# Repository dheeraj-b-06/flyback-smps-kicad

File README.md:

# 12V 5A (60 W) Isolated Flyback SMPS

An offline, isolated switch-mode power supply designed in **KiCad 9.0**. It converts AC mains into a regulated **12 V DC output at up to 5 A** using a flyback converter with secondary-side regulation (TL431 + optocoupler).

> ⚠️ **Mains voltage warning:** this circuit connects directly to AC mains and has lethal voltages (up to ~400 V DC) on the primary side. Only build or test it if you are experienced with mains-connected electronics.

## Specifications

| Parameter | Value |
|---|---|
| Output | 12 V DC, 5 A (60 W) |
| Topology | Isolated flyback |
| PWM controller | OB2273 (current-mode, SOT-23-6) |
| Power switch | SVF12N65F (650 V N-MOSFET) |
| Transformer | EFD30 core, custom wound |
| Output rectifier | MBRF30100 dual Schottky |
| Feedback | TL431 + EL817C optocoupler |
| Primary-secondary clearance | 6 mm (enforced by custom DRC rules) |
| PCB | 2-layer, 1.6 mm |

## Block diagram

```mermaid
flowchart LR
    AC[AC mains] --> IN[Fuse, NTC, varistor,<br/>X-cap, CM choke]
    IN --> BR[Bridge rectifier<br/>+ 400 V bulk cap]
    BR --> T[Flyback transformer T2]
    T --> Q[MOSFET Q1]
    Q --> RS[Sense resistor R8]
    T --> D[Schottky D4]
    D --> F[LC filter<br/>+ output caps]
    F --> OUT[12 V / 5 A]
    F --> TL[TL431 voltage divider]
    TL --> OPT[Optocoupler EL817C]
    OPT -->|FB| IC[OB2273 PWM controller]
    RS -->|current sense| IC
    IC -->|gate drive| Q
    T -.->|aux winding| IC
```

## How it works

### 1. Input stage and rectification
Mains enters through terminal block **J1** and a **1 A fuse (F1)**. The **varistor (R1)** clamps surges, the **X-capacitor (C1, 100 nF / 275 VAC)** and the **common-mode choke (T1)** filter conducted noise, and the **NTC thermistor (R2)** limits the inrush current when the bulk capacitor charges. The **KBP410 bridge (BR1)** rectifies the AC and the **120 µF / 400 V capacitor (C2)** smooths it into a high-voltage DC rail (the `DCLINE` net, roughly 310–340 V DC at 230 V AC input).

### 2. Start-up and controller supply
When power is first applied, the OB2273 has no supply. **R3 and R4** (470 kΩ each, in series) trickle current from the DC rail into the VDD pin, charging **C5 (47 µF)** and **C6 (1 µF)**. Once VDD reaches the start-up threshold, the controller begins switching.

After start-up, the **auxiliary winding** on T2 (pins 4 and 6) takes over: diode **D2 (FR107)** and resistor **R9** rectify it to keep VDD alive without the wasteful start-up resistors. **D3 (24 V zener)** clamps VDD to protect the controller from overvoltage.

### 3. Switching and energy transfer (flyback action)
The OB2273 is a current-mode PWM controller. Its switching frequency is set by **R10** (100 kΩ) on the RI pin. It drives the gate of **Q1 (SVF12N65F)** through gate resistor **R6 (10 Ω)**.

- **MOSFET ON:** current ramps up through the primary winding of T2 and energy is stored in the transformer core. The secondary diode is reverse-biased, so the output capacitors alone supply the load.
- **MOSFET OFF:** the transformer voltage reverses, the Schottky **D4 (MBRF30100)** conducts, and the stored energy is delivered to the secondary, charging the output capacitors and feeding the load.

The transformer provides **galvanic isolation** between the mains-side primary and the safe-voltage secondary.

### 4. Current sensing and protection
Primary current flows through **R8 (0.2 Ω)** to ground. The resulting voltage is fed to the SENSE pin through **R7 (100 Ω)** and **C4 (100 pF)**, which form a low-pass filter that suppresses the turn-on spike. The controller ends each cycle when the peak current reaches its limit, giving **cycle-by-cycle overcurrent protection**.

### 5. Snubber / clamp
When Q1 turns off, the transformer's leakage inductance causes a voltage spike on the drain. The **RCD clamp** formed by **D1 (FR207), R5 (33 kΩ) and C3 (3.3 nF / 630 V)** absorbs this energy, keeping the drain voltage within the MOSFET's 650 V rating.

### 6. Output filtering
The Schottky output is smoothed by **C10 (2200 µF) and C11 (1000 µF)**, then passed through the **3.3 µH inductor (L1)** and **C12 (470 µF)** to reduce high-frequency ripple. **R16 (470 Ω)** acts as a small preload, and **R17 with LED D5** gives a power-on indicator.

### 7. Voltage regulation (feedback loop)
The output voltage is regulated on the secondary side:

1. A resistor divider (**R13** from the output, **R14** and trimmer **R15** to ground) feeds a fraction of the output voltage to the reference pin of the **TL431 (U1)**. The output voltage is set by

   `Vout ≈ Vref × (1 + R13 / R_bottom)`, where Vref ≈ 2.5 V

   and the **trimmer R15 fine-tunes** the final output.
2. If the output rises above target, the TL431 conducts harder and increases the current through the **optocoupler LED (OP1)**. Resistors **R11 and R12** set the bias, and **C8 (100 nF)** provides loop compensation.
3. The optocoupler's transistor pulls the controller's **FB pin** down, filtered by **C7 (10 nF)**, which tells the OB2273 to deliver less energy per cycle. If the output falls, the opposite happens.

Because the optocoupler transmits the error signal by light, the feedback loop crosses the isolation barrier without any electrical connection.

### 8. Isolation and EMI
The primary ground (`GND-1`) and secondary ground (`GND-2`) are separate. The only deliberate bridge between them is the **Y-capacitor C9 (2.2 nF / 250 VAC)**, which provides a return path for common-mode noise. Custom KiCad design rules enforce a **6 mm clearance** between primary-side and secondary-side copper.

## Key components

| Ref | Part | Function |
|---|---|---|
| F1 | 1 A fuse | Overcurrent protection |
| R1 | Varistor B72207S0271K101 | Surge protection |
| R2 | NTC 5D-11 | Inrush current limiting |
| C1 | 100 nF / 275 VAC | X-capacitor (differential EMI filter) |
| T1 | UU9.8 common-mode choke | Common-mode EMI filter |
| BR1 | KBP410 | Bridge rectifier |
| C2 | 120 µF / 400 V | Bulk capacitor |
| IC1 | OB2273 | Current-mode PWM controller |
| Q1 | SVF12N65F | 650 V power MOSFET |
| R8 | 0.2 Ω | Primary current sense |
| D1, R5, C3 | FR207, 33 kΩ, 3.3 nF | RCD snubber / clamp |
| T2 | EFD30 (6+6) | Flyback transformer (isolation) |
| D4 | MBRF30100 | Secondary Schottky rectifier |
| C10, C11, C12, L1 | 2200 µF, 1000 µF, 470 µF, 3.3 µH | Output filter |
| U1 | TL431 | Voltage reference / error amplifier |
| OP1 | EL817C | Optocoupler (isolated feedback) |
| R15 | 1 kΩ trimmer | Output voltage adjustment |
| C9 | 2.2 nF / 250 VAC | Y-capacitor |

## Repository contents

| File / folder | Description |
|---|---|
| `SMPS_12V_5A.kicad_sch` | Schematic |
| `SMPS_12V_5A.kicad_pcb` | PCB layout |
| `SMPS_12V_5A.kicad_pro` | KiCad project file |
| `SMPS_12V_5A.kicad_dru` | Custom design rules (isolation clearance) |
| `libs/lcsc/` | Imported LCSC symbols, footprints and 3D models |
| `mysmps.pretty/` | Custom footprints (transformer, 400 V capacitor) |

Open `SMPS_12V_5A.kicad_pro` in KiCad 9.0 or newer to view the design.

## Status

- [x] Schematic
- [x] PCB layout
- [ ] Prototype built
- [ ] Full-load testing

## Author

**Dheeraj**

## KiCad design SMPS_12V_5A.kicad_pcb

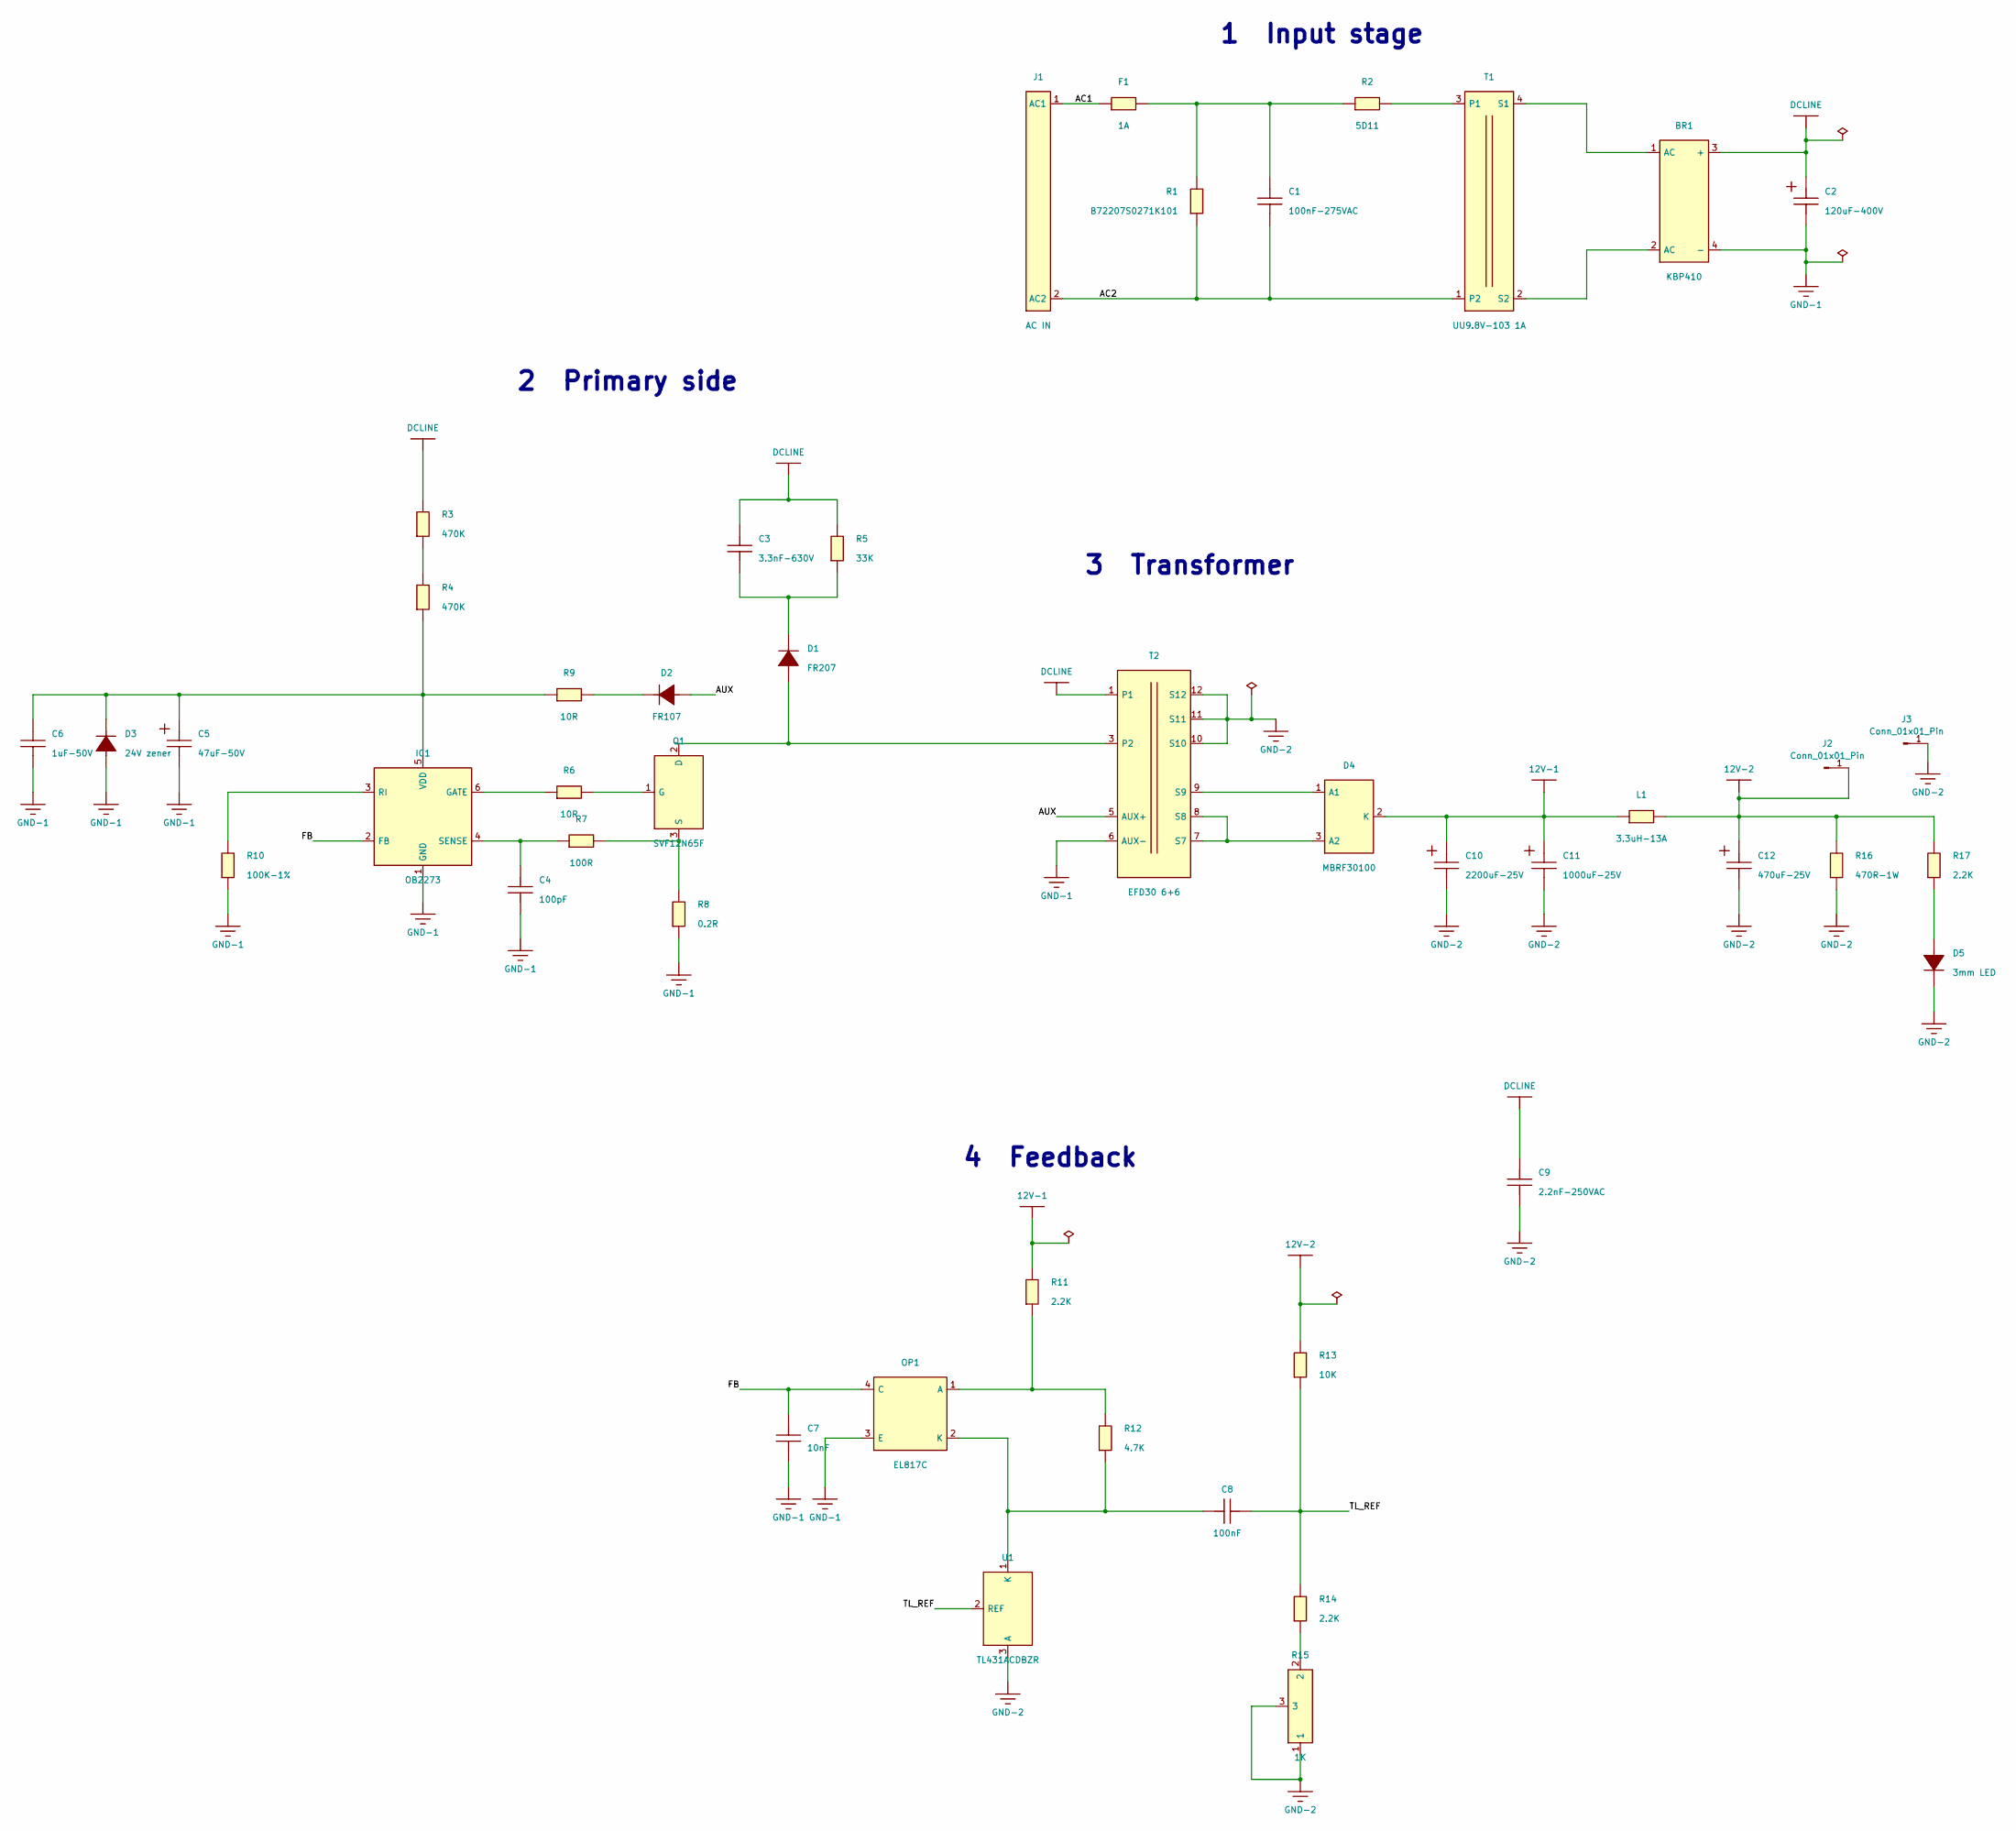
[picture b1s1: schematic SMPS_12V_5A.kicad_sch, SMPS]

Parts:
BR1: KBP410; C382768_KBP_4P-L14_5-W3_5-P3_81-L
C1: 100nF-275VAC; C_Rect_L18.0mm_W6.0mm_P15.00mm_FKS3_FKP3
C2: 120uF-400V; C_Box_P7.62mm_18x32.5mm
C3: 3.3nF-630V; C_1206_3216Metric
C4: 100pF; C_0805_2012Metric
C5: 47uF-50V; C_Radial_D6.3mm_H7.0mm_P2.50mm
C6: 1uF-50V; C_0805_2012Metric
C7: 10nF; C_0805_2012Metric
C8: 100nF; C_0805_2012Metric
C9: 2.2nF-250VAC; C_Disc_D7.0mm_W2.5mm_P5.00mm
C10: 2200uF-25V; C_Radial_D12.5mm_H20.0mm_P5.00mm
C11: 1000uF-25V; C_Radial_D10.0mm_H12.5mm_P5.00mm
C12: 470uF-25V; C_Radial_D8.0mm_H7.0mm_P3.50mm
D1: FR207; D_DO-15_P12.70mm_Horizontal
D2: FR107; D_DO-41_SOD81_P10.16mm_Horizontal
D3: 24V zener; D_MiniMELF
D4: MBRF30100; TO-220F-3_Vertical
D5: 3mm LED; LED_D3.0mm
F1: 1A; C3098_FUSE-TH_L8_5-W4_0-P5_08-D0_6
IC1: OB2273; SOT-23-6
J1: AC IN; TerminalBlock_bornier-2_P5.08mm
J2, J3: Conn_01x01_Pin; SolderWire-1.5sqmm_1x01_D1.7mm_OD3mm
L1: 3.3uH-13A; L_Wuerth_HCI-1350
OP1: EL817C; DIP-4_W7.62mm
Q1: SVF12N65F; TO-220F-3_Vertical
R1: B72207S0271K101; C125493_RES-TH_L9_0-W4_6-P5_00-D0_9-S3_4
R2: 5D11; RV_Disc_D9mm_W3.8mm_P5mm
R3, R4: 470K; R_1206_3216Metric
R5: 33K; R_2512_6332Metric
R6: 10R; R_0805_2012Metric
R7: 100R; R_0805_2012Metric
R8: 0.2R; R_2512_6332Metric
R9: 10R; R_1206_3216Metric
R10: 100K-1%; R_0805_2012Metric
R11, R14, R17: 2.2K; R_0805_2012Metric
R12: 4.7K; R_0805_2012Metric
R13: 10K; R_0805_2012Metric
R15: 1K; Potentiometer_Bourns_3296W_Vertical
R16: 470R-1W; R_2512_6332Metric
T1: UU9.8V-103 1A; C5276603_FILTER-TH_CMI-UU9_8-25MH
T2: EFD30 6+6; Transformer_EE_12pin_P5.08mm_Row27.56mm
U1: TL431ACDBZR; SOT-23

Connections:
12V-1: C10.1, C11.1, D4.2 (K), L1.1, R11.1
12V-2: C12.1, J2.1, L1.2, R13.1, R16.1, R17.1
/AC1: F1.1, J1.1 (AC1)
/AC2: C1.2, J1.2 (AC2), R1.2, T1.1 (P2)
/AUX: D2.2, T2.5 (AUX+)
/FB: C7.1, IC1.2 (FB), OP1.4 (C)
/TL_REF: C8.2, R13.2, R14.1, U1.2 (REF)
DCLINE: BR1.3 (+), C2.1, C3.1, C9.1, R3.1, R5.1, T2.1
GND-1: BR1.4 (-), C2.2, C4.2, C5.2, C6.2, C7.2, D3.2, IC1.1 (GND), OP1.3 (E), R8.2, R10.2, T2.6 (AUX-)
GND-2: C9.2, C10.2, C11.2, C12.2, D5.1, J3.1, R15.1, R15.3, R16.2, T2.10 (S10), T2.11 (S11), T2.12 (S12), U1.3 (A)
unnamed: C1.1, F1.2, R1.1, R2.1
unnamed: C3.2, D1.1, R5.2
unnamed: D2.1, R9.2
unnamed: D4.1 (A1), T2.9 (S9)
unnamed: D4.3 (A2), T2.7 (S7), T2.8 (S8)
unnamed: D5.2, R17.2
unnamed: IC1.6 (GATE), R6.1
unnamed: IC1.3 (RI), R10.1
unnamed: C4.1, IC1.4 (SENSE), R7.1
unnamed: C5.1, C6.1, D3.1, IC1.5 (VDD), R4.2, R9.1
unnamed: OP1.1 (A), R11.2, R12.1
unnamed: C8.1, OP1.2 (K), R12.2, U1.1 (K)
unnamed: D1.2, Q1.2 (D), T2.3 (P2)
unnamed: Q1.1 (G), R6.2
unnamed: Q1.3 (S), R7.2, R8.1
unnamed: R3.2, R4.1
unnamed: R14.2, R15.2
unnamed: R2.2, T1.3 (P1)
unnamed: BR1.1 (AC), T1.4 (S1)
unnamed: BR1.2 (AC), T1.2 (S2)

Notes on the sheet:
2 Primary side
1 Input stage
3 Transformer
4 Feedback

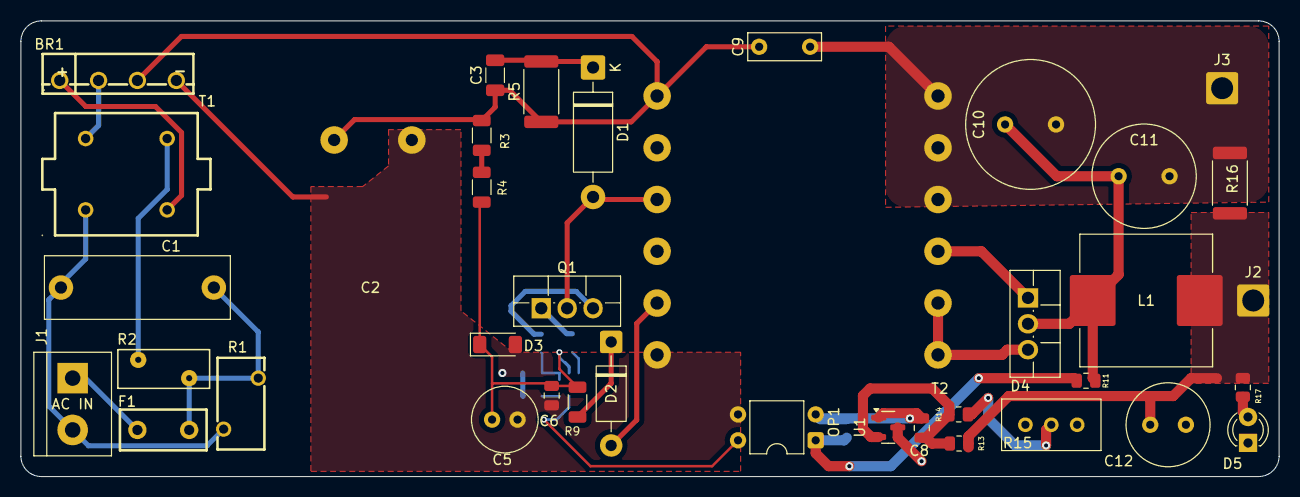
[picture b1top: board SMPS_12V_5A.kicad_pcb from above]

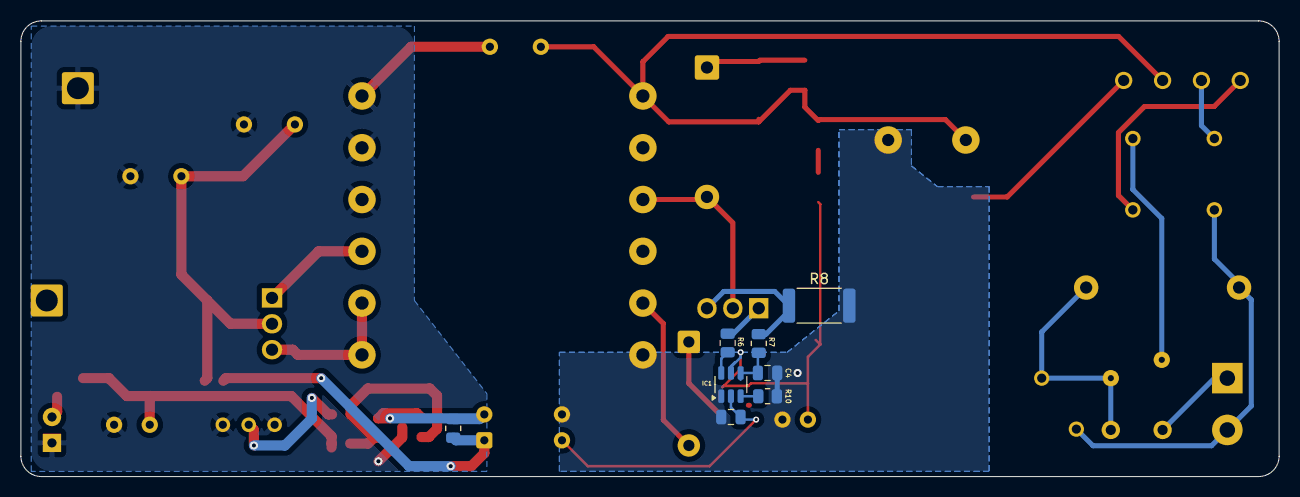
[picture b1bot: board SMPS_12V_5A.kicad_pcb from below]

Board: 2 copper layers, 123.4 x 44.7 mm, 46 parts (8 on the bottom side), 30 nets.
